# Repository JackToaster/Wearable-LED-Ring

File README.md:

# Wearable LED Ring
This project is intended to be a wearable ring with integrated batteries, LEDs, microphone, and microcontroller.

## PCB
(still WIP)

## Firmware
The ring uses an STM32L431CCYxxx microcontroller

(todo port ColorChord embedded)

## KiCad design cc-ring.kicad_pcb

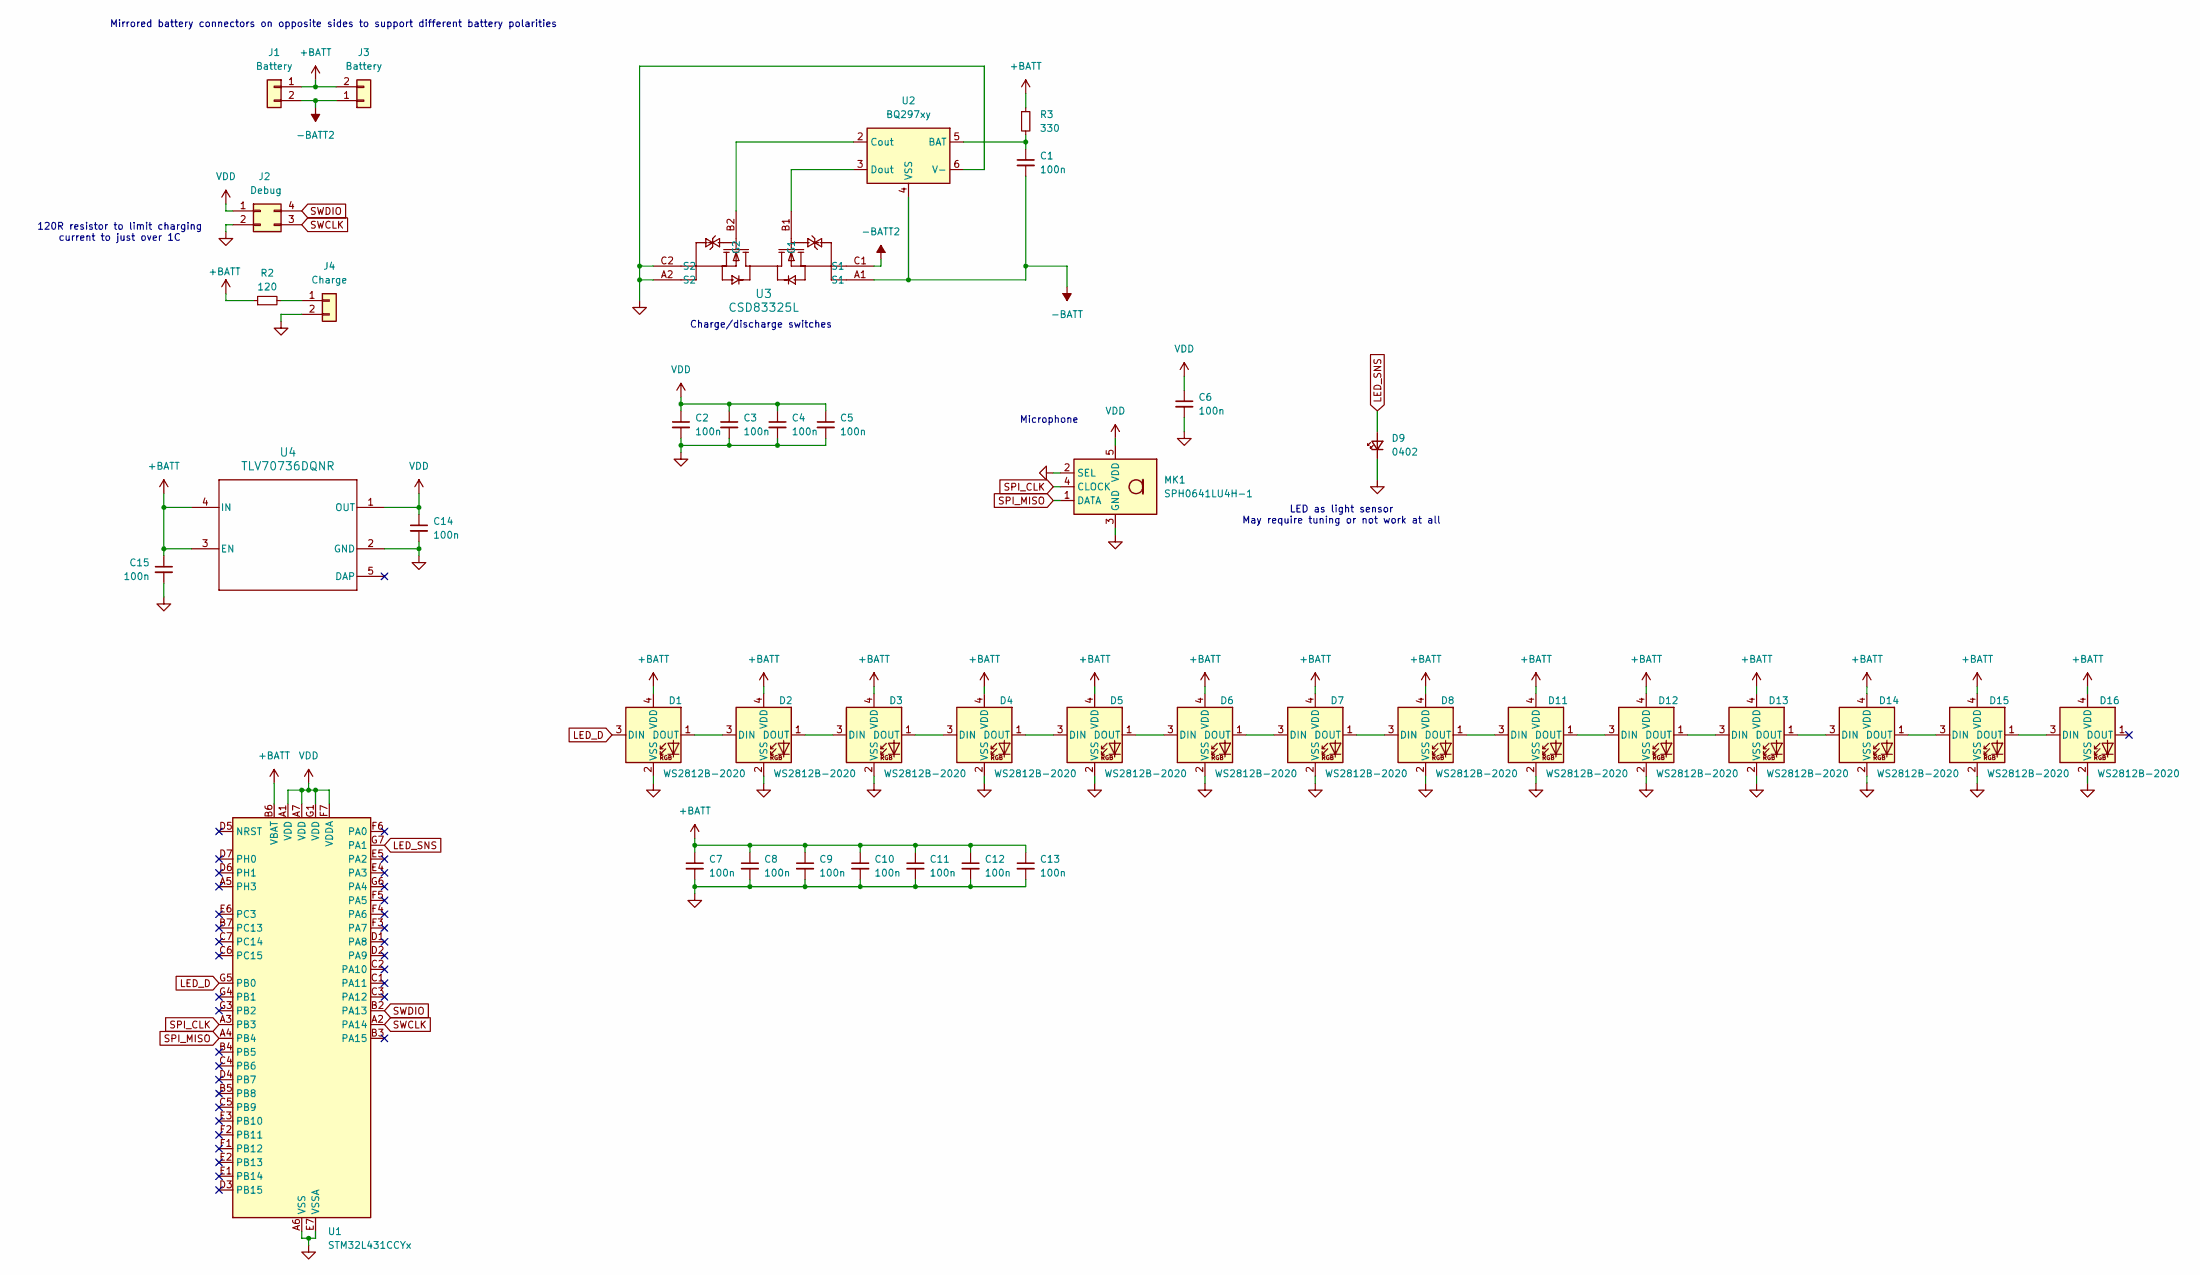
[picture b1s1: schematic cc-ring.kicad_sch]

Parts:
C1, C2, C3, C4, C5, C6, C7, C8, C9, C10, C11, C12, C13, C14, C15: 100n; C_0402_1005Metric
D1, D2, D3, D4, D5, D6, D7, D8, D11, D12, D13, D14, D15, D16: WS2812B-2020; LED_WS2812B-2020_PLCC4_2.0x2.0mm
D9: 0402; LED_0402_1005Metric
J1, J3: Battery
J2: Debug; BGA-4_2x2_3.0x3.0mm
J4: Charge; MageneticChargeConnector
MK1: SPH0641LU4H-1; Knowles_LGA-5_3.5x2.65mm
R2: 120; R_0402_1005Metric
R3: 330; R_0402_1005Metric
U1: STM32L431CCYx; ST_WLCSP-49_Die435
U2: BQ297xy; WSON-6_1.5x1.5mm_P0.5mm
U3: CSD83325L; YJE0006A
U4: TLV70736DQNR; DQN0004A

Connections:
+BATT: C7.1, C8.1, C9.1, C10.1, C11.1, C12.1, C13.1, C15.1, D1.4 (VDD), D2.4 (VDD), D3.4 (VDD), D4.4 (VDD), D5.4 (VDD), D6.4 (VDD), D7.4 (VDD), D8.4 (VDD), D11.4 (VDD), D12.4 (VDD), D13.4 (VDD), D14.4 (VDD), D15.4 (VDD), D16.4 (VDD), J1.1, J3.2, R2.1, R3.1, U1.B6 (VBAT), U4.3 (EN), U4.4 (IN)
-BATT: C1.2, U2.4 (VSS), U3.A1 (S1)
-BATT2: J1.2, J3.1, U3.C1 (S1)
GND: C2.2, C3.2, C4.2, C5.2, C6.2, C7.2, C8.2, C9.2, C10.2, C11.2, C12.2, C13.2, C14.2, C15.2, D1.2 (VSS), D2.2 (VSS), D3.2 (VSS), D4.2 (VSS), D5.2 (VSS), D6.2 (VSS), D7.2 (VSS), D8.2 (VSS), D9.1 (K), D11.2 (VSS), D12.2 (VSS), D13.2 (VSS), D14.2 (VSS), D15.2 (VSS), D16.2 (VSS), J2.2, J4.2, MK1.2 (SEL), MK1.3 (GND), U1.A6 (VSS), U1.B1 (VSS), U1.E7 (VSSA), U1.G2 (VSS), U2.6 (V-), U3.A2 (S2), U3.C2 (S2), U4.2 (GND)
LED_D: D1.3 (DIN), U1.G5 (PB0)
LED_SNS: D9.2 (A), U1.G7 (PA1)
unnamed: D1.1 (DOUT), D2.3 (DIN)
unnamed: D2.1 (DOUT), D3.3 (DIN)
unnamed: D3.1 (DOUT), D4.3 (DIN)
unnamed: D4.1 (DOUT), D5.3 (DIN)
unnamed: D5.1 (DOUT), D6.3 (DIN)
unnamed: D6.1 (DOUT), D7.3 (DIN)
unnamed: D7.1 (DOUT), D8.3 (DIN)
unnamed: D8.1 (DOUT), D11.3 (DIN)
unnamed: D11.1 (DOUT), D12.3 (DIN)
unnamed: D12.1 (DOUT), D13.3 (DIN)
unnamed: D13.1 (DOUT), D14.3 (DIN)
unnamed: D14.1 (DOUT), D15.3 (DIN)
unnamed: D15.1 (DOUT), D16.3 (DIN)
unnamed: J4.1, R2.2
unnamed: C1.1, R3.2, U2.5 (BAT)
unnamed: U2.2 (Cout), U3.B2 (G2)
unnamed: U2.3 (Dout), U3.B1 (G1)
SPI_CLK: MK1.4 (CLOCK), U1.A3 (PB3)
SPI_MISO: MK1.1 (DATA), U1.A4 (PB4)
SWCLK: J2.3, U1.A2 (PA14)
SWDIO: J2.4, U1.B2 (PA13)
VDD: C2.1, C3.1, C4.1, C5.1, C6.1, C14.1, J2.1, MK1.5 (VDD), U1.A1 (VDD), U1.A7 (VDD), U1.F7 (VDDA), U1.G1 (VDD), U4.1 (OUT)

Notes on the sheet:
LED as light sensor May require tuning or not work at all
Charge/discharge switches
Mirrored battery connectors on opposite sides to support different battery polarities
Microphone
120R resistor to limit charging current to just over 1C

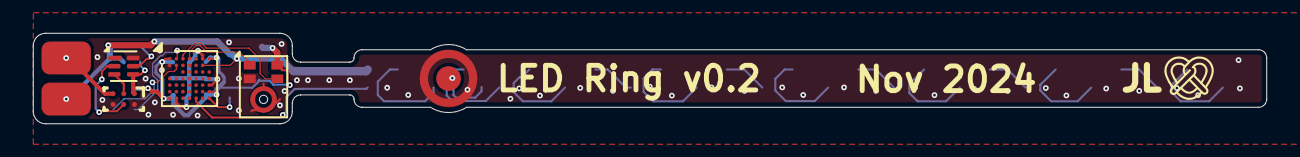
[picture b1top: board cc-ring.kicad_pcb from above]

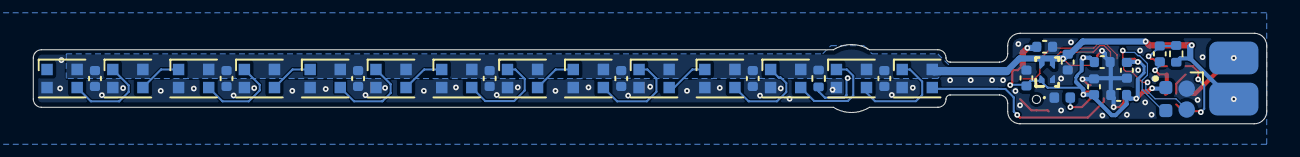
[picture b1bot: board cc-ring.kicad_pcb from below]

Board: 2 copper layers, 75.0 x 5.5 mm, 41 parts (35 on the bottom side), 28 nets.

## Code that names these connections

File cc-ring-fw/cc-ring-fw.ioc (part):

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Mcu.Name=STM32L431C(B-C)Yx
Mcu.Package=WLCSP49
Mcu.UserName=STM32L431CCYx
PA1.GPIOParameters=GPIO_PuPd,GPIO_Label,GPIO_ModeDefaultOutputPP
PA1.GPIO_Label=led
PA1.GPIO_ModeDefaultOutputPP=GPIO_MODE_OUTPUT_OD
PA1.GPIO_PuPd=GPIO_PULLUP
PA1.Signal=GPIO_Output
PA13\ (JTMS-SWDIO).Mode=Serial_Wire
PA13\ (JTMS-SWDIO).Signal=SYS_JTMS-SWDIO
PA14\ (JTCK-SWCLK).Mode=Serial_Wire
PA14\ (JTCK-SWCLK).Signal=SYS_JTCK-SWCLK
PB0.GPIOParameters=GPIO_Label
PB0.GPIO_Label=led_dat
PB0.Signal=GPIO_Output
PB3\ (JTDO-TRACESWO).Mode=RX_Only_Simplex_Unidirect_Master
PB3\ (JTDO-TRACESWO).Signal=SPI1_SCK
PB4\ (NJTRST).Mode=RX_Only_Simplex_Unidirect_Master
PB4\ (NJTRST).Signal=SPI1_MISO
RCC.HSE_VALUE=8000000
RCC.SYSCLKFreq_VALUE=80000000
RCC.SYSCLKSource=RCC_SYSCLKSOURCE_PLLCLK
board=custom

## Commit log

2024-10-12 initial commit/layout
2024-10-26 magnetic charge connector
2024-10-26 update layout for magentic charge
2024-10-26 small layout tweaks, add dxf
2024-11-08 make it manufacturable lol
2024-12-28 port colorchord :D
